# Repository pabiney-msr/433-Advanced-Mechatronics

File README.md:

# ME433_2017

Course website for Advanced Mechatronics at NU in Spring 2017

All information is on the git wiki! https://github.com/ndm736/ME433_2017/wiki

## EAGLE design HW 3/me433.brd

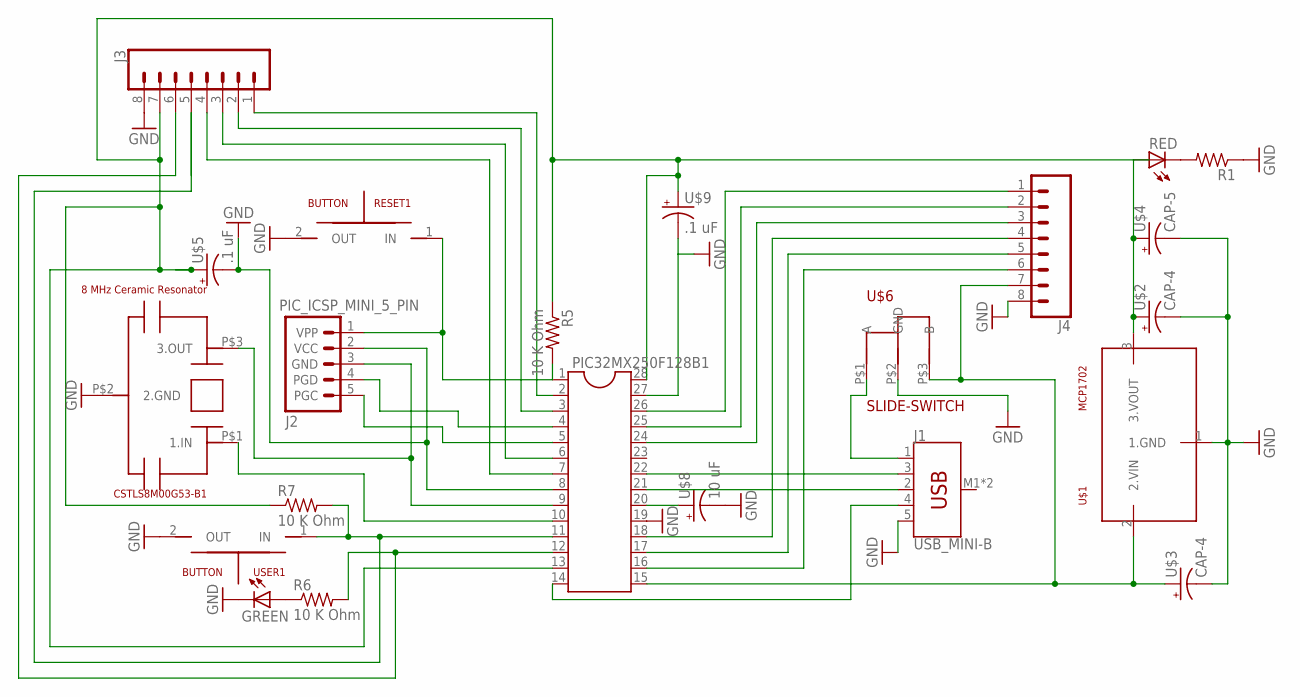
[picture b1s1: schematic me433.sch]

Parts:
CSTLS8M00G53-B1: 8 MHz Ceramic Resonator; CSTLS8M00G53-B0
GREEN: LED3MM
J1: USB_MINI-B; 32005-601
J2: PIC_ICSP_MINI_5_PIN
J3, J4: CONN_08"; 1X08
PIC32MX250F128B1: DIL28-3
R1: R-US_0207/10; 0207/10
R5, R6, R7: 10 K Ohm; 0207/10
RED: LED3MM
RESET1: BUTTON
U$1: MCP1702; TO92
U$2, U$3: CAP-4; E1,8-4
U$4: CAP-5; E2,5-5
U$5, U$9: .1 uF; E1,8-4
U$6: SLIDE-SWITCH; ALCOSWITCH
U$8: 10 uF; E2,5-5
USER1: BUTTON

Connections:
GND: CSTLS8M00G53-B1.P$2 (2.GND), GREEN.K (C), J1.5 (GND), J2.2 (VCC), J3.8, J4.8, PIC32MX250F128B1.8, PIC32MX250F128B1.19, R1.1, RESET1.2 (OUT), U$1.1 (1.GND), U$2.-, U$3.-, U$4.-, U$5.-, U$6.P$2 (GND), U$8.-, U$9.-, USER1.2 (OUT)
unnamed: R1.2, RED.K (C)
unnamed: CSTLS8M00G53-B1.P$3 (3.OUT), J2.3 (GND), PIC32MX250F128B1.9
unnamed: CSTLS8M00G53-B1.P$1 (1.IN), PIC32MX250F128B1.10
unnamed: J4.7, PIC32MX250F128B1.15, U$1.2 (2.VIN), U$3.+, U$6.P$3 (B)
unnamed: J1.2 (D+), PIC32MX250F128B1.21
unnamed: J3.7, PIC32MX250F128B1.13, PIC32MX250F128B1.28, R5.1, R7.1, RED.A, U$1.3 (3.VOUT), U$2.+, U$4.+, U$5.+, U$9.+
unnamed: PIC32MX250F128B1.20, U$8.+
unnamed: J2.4 (PGD), PIC32MX250F128B1.4
unnamed: GREEN.A, R6.1
unnamed: J3.3, PIC32MX250F128B1.6
unnamed: J3.5, PIC32MX250F128B1.11, R7.2, USER1.1 (IN)
unnamed: J1.3 (D-), PIC32MX250F128B1.22
unnamed: J1.4 (ID), PIC32MX250F128B1.14
unnamed: J3.1, PIC32MX250F128B1.2
unnamed: J2.5 (PGC), PIC32MX250F128B1.5
unnamed: J1.1 (VBUS), U$6.P$1 (A)
unnamed: J4.6, PIC32MX250F128B1.16
unnamed: J3.4, PIC32MX250F128B1.7
unnamed: J3.6, PIC32MX250F128B1.12, R6.2
unnamed: J4.1, PIC32MX250F128B1.26
unnamed: J4.2, PIC32MX250F128B1.25
unnamed: J4.3, PIC32MX250F128B1.24
unnamed: J4.5, PIC32MX250F128B1.17
unnamed: J4.4, PIC32MX250F128B1.18
unnamed: J3.2, PIC32MX250F128B1.3
unnamed: J2.1 (VPP), R5.2, RESET1.1 (IN)

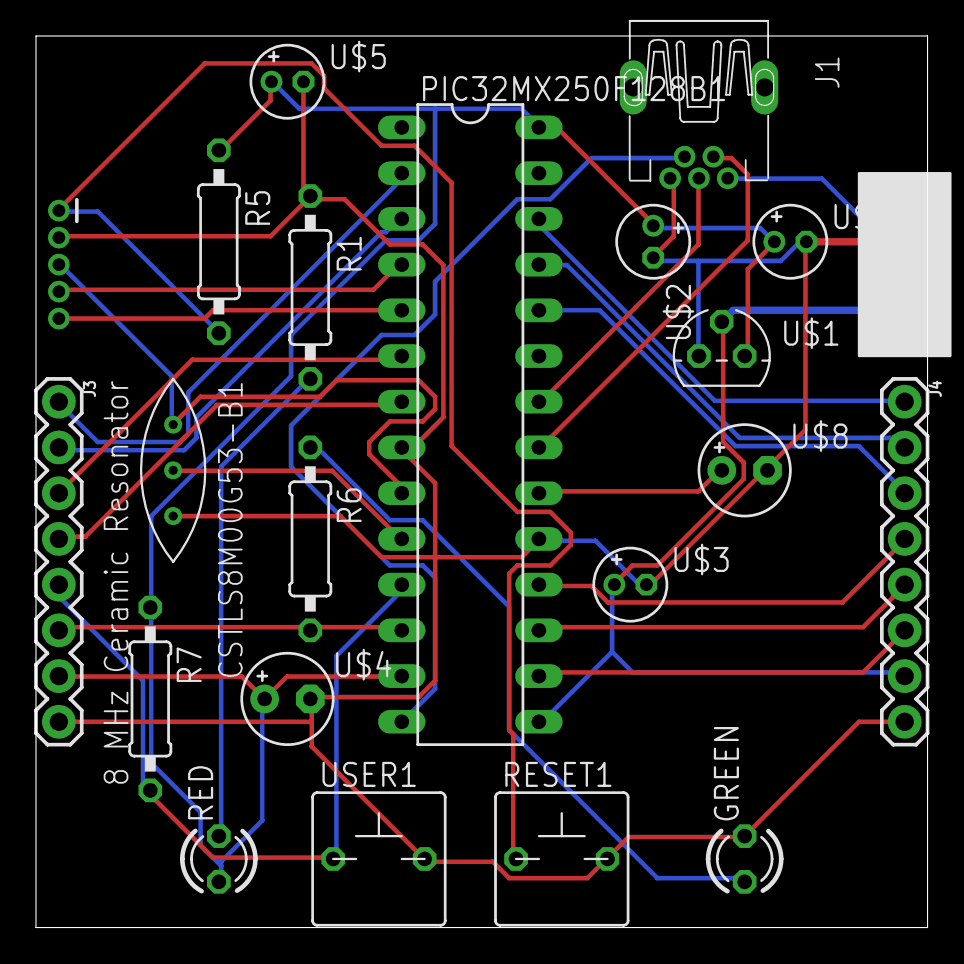
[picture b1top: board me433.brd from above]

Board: 2 copper layers, 49.5 x 49.5 mm, 22 parts (0 on the bottom side), 27 nets.

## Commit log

2017-03-30 HW1 Question 1
2017-03-30 Added more provided materials
2017-03-30 Question 2 Both screenshots included. Both capacitors were needed to make the signal flatline.
2017-03-30 removed content that i had added because I thought it was course content but now I am thinking it might have been a students submit to the original by mistake.
2017-03-30 Questions 1 & 2 fixed, Question 6 added
2017-03-30 missed these 2 files
2017-03-30 First Code Commit
2017-03-30 green LED flickers correctly
2017-03-30 light working, code for button
2017-04-02 fixed the button and the light and circuit diagram
2017-04-04 HW 2
2017-05-15 Gerber Files Generated
    Pushing HW 3 andthe generated gerber files.
2017-05-29 HW 4
2017-05-29 HW 4 Waves
    Image ofthe Sin and Tri Waves
2017-05-29 HW 5
2017-05-29 HW 6
2017-05-30 Changed Pin
2017-05-30 Edited images
2017-06-02 HW 7
2017-06-02 HW 8 Part 1
2017-06-02 HW 8 Part 2
2017-06-04 HW 15
2017-06-05 HW 9
2017-06-05 HW 12
2017-06-05 HW 12 Part 2
2017-06-05 HW 13
2017-06-05 Started HW 10
2017-06-05 Removing HW 9/HW 9
2017-06-06 HW 10
2017-06-06 HW 11 Part 1
2017-06-06 HW 11
2017-06-07 HW 14
2017-06-07 HW 18
2017-06-07 HW 18 Brushed Motor Code
2017-06-07 HW 18 Servo Code
2017-06-07 Git Ignore
2017-06-07 HW 1
2017-06-07 HW 17
2017-06-08 HW 19
2017-06-10 HW 16
2017-06-12 HW 20

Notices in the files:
parts and their libraries:
SparkFun-Connectors: Licensing: Creative Commons ShareAlike 4.0 International - https://creativecommons.org/licenses/by-sa/4.0
